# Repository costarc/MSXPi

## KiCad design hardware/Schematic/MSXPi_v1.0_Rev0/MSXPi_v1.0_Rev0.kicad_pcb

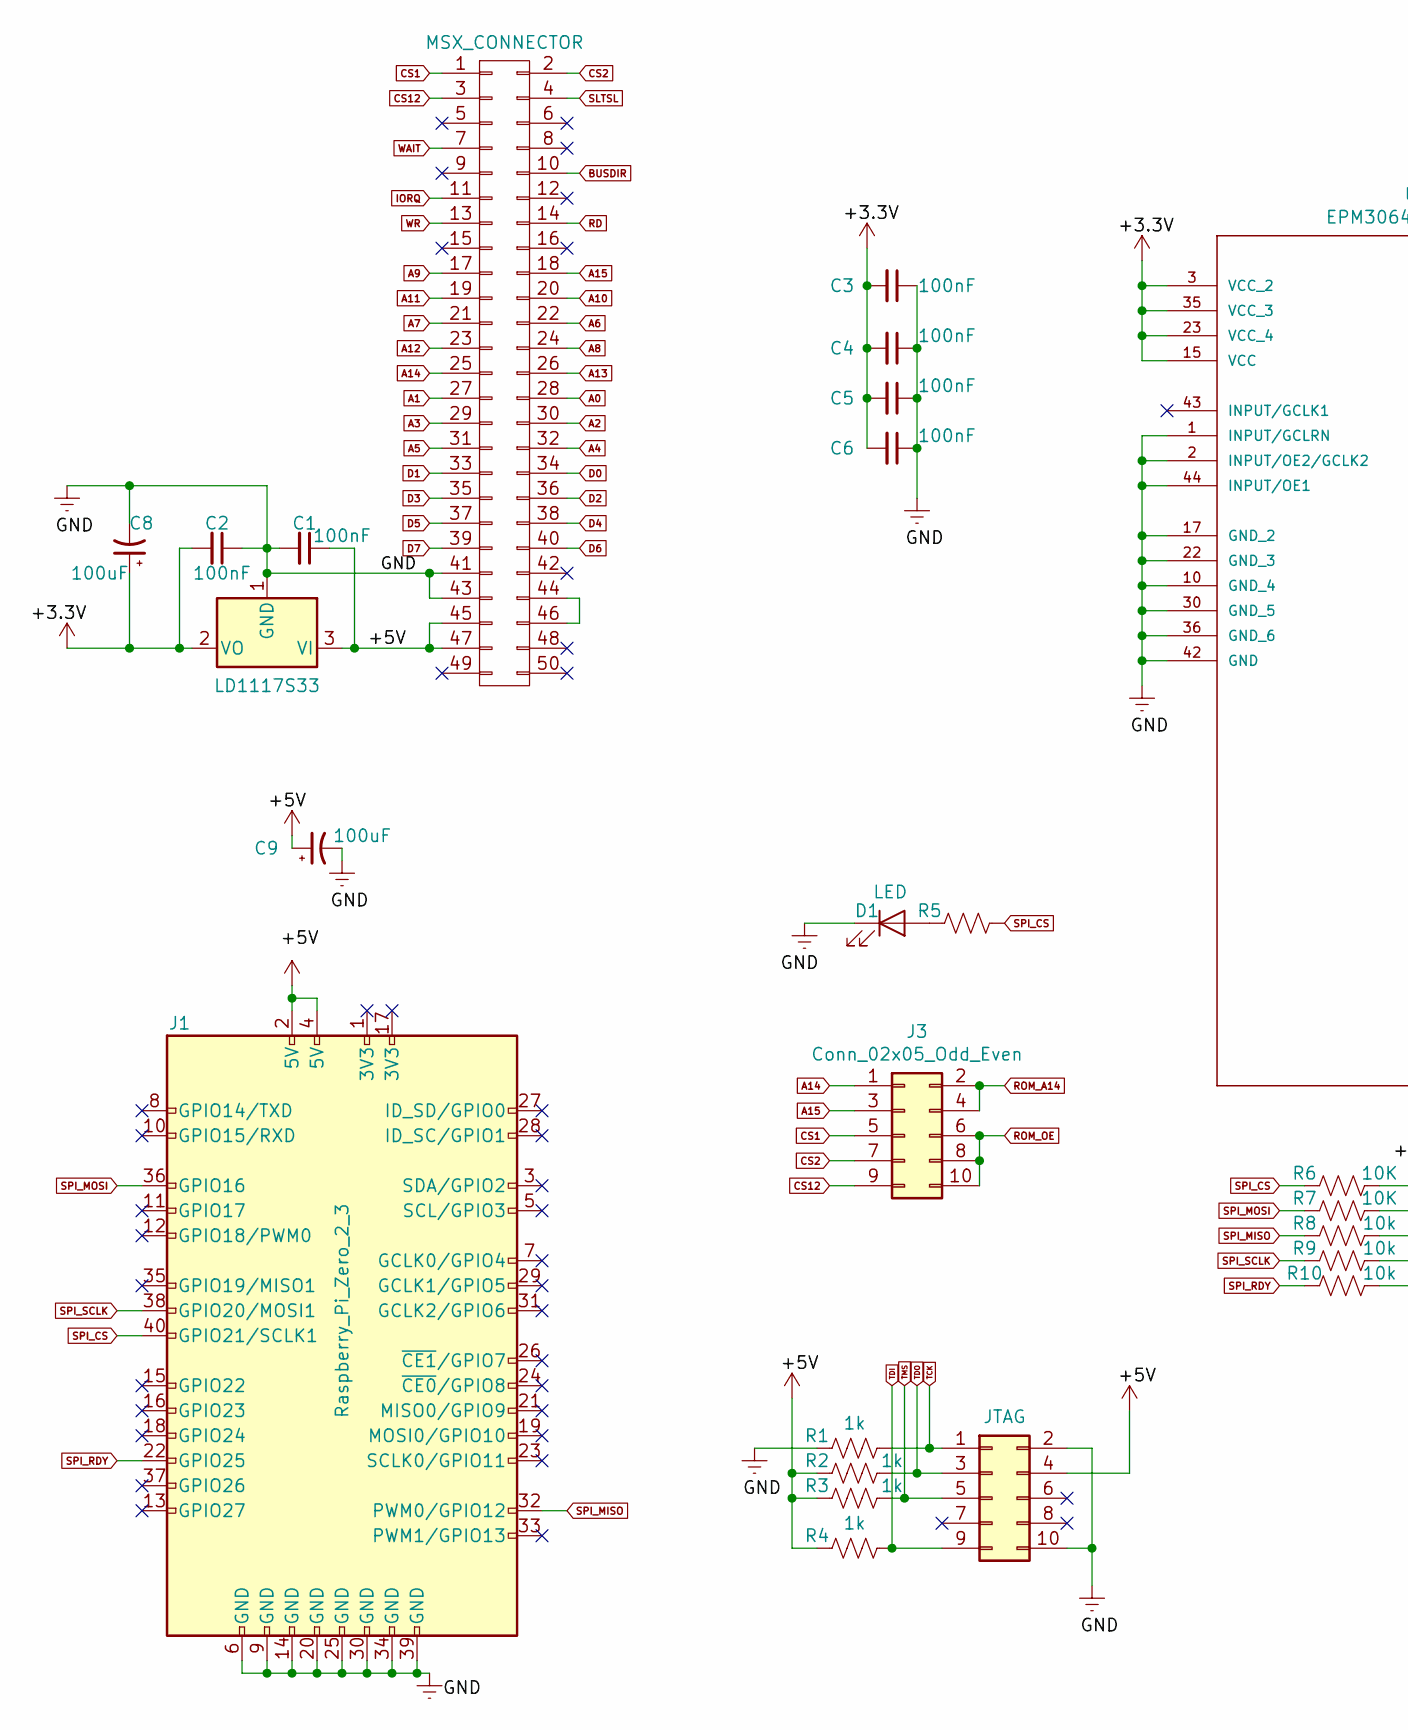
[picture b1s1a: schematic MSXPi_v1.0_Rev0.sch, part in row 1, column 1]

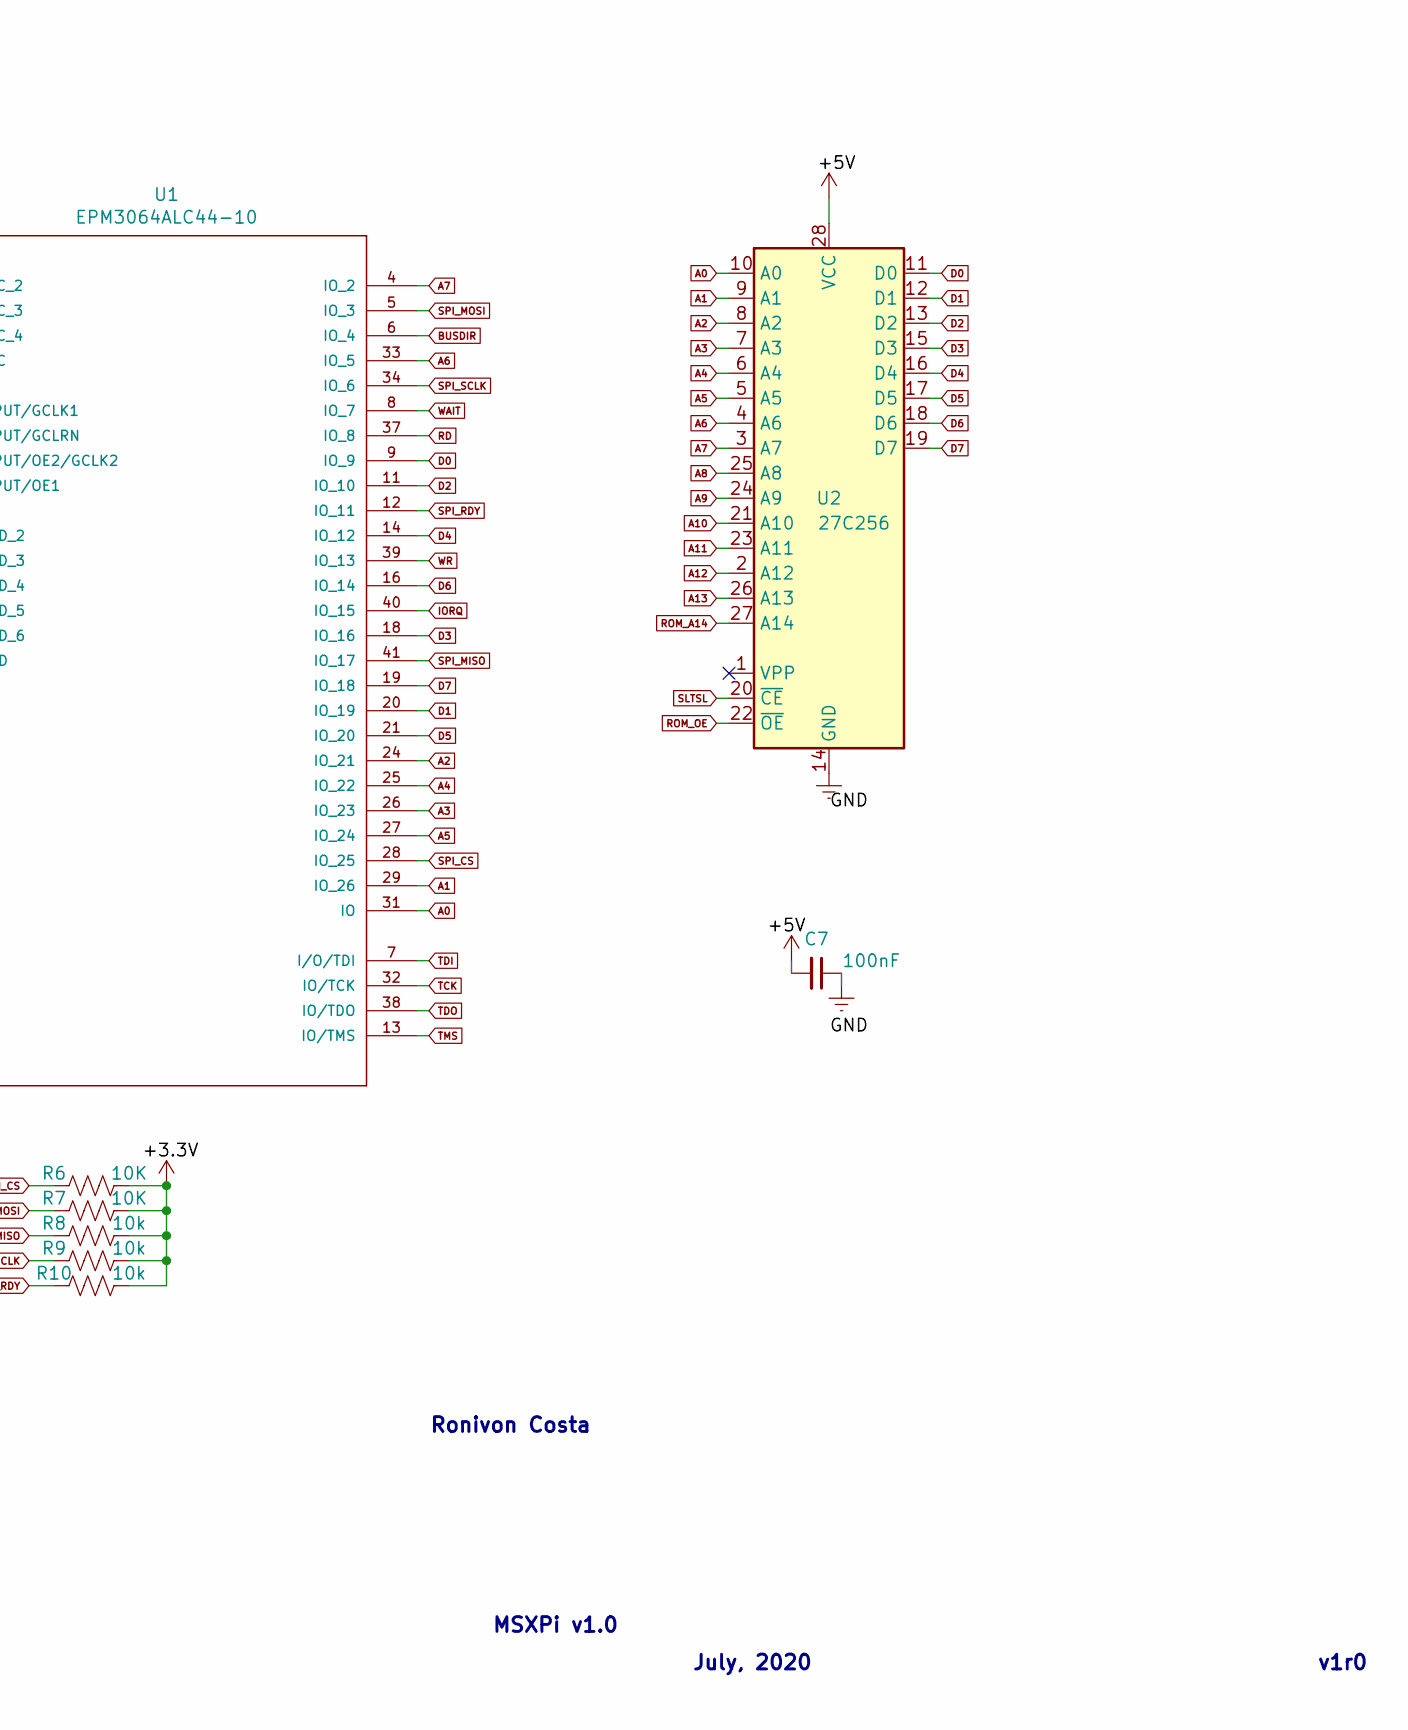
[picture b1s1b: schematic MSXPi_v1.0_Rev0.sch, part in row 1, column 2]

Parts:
C1, C2, C3, C4, C5, C6, C7: 100nF; C_Disc_D3.0mm_W1.6mm_P2.50mm
C8, C9: 100uF; CP_Radial_D5.0mm_P2.50mm
D1: LED; LED_D3.0mm
J1: Raspberry_Pi_Zero_2_3; PinHeader_2x20_P2.54mm_Vertical
J2: JTAG; IDC-Header_2x05_P2.54mm_Horizontal
J3: Conn_02x05_Odd_Even; JST_PHD_B10B-PHDSS_2x05_P2.00mm_Vertical
LD1117S33: LD1117S33TR_SOT223; SOT-223-3_TabPin2
P1: MSX_CONNECTOR; card_edge_connector
R1, R2, R3, R4: 1k; R_Axial_DIN0204_L3.6mm_D1.6mm_P5.08mm_Horizontal
R5: R_US; R_Axial_DIN0204_L3.6mm_D1.6mm_P5.08mm_Horizontal
R6, R7: 10K; R_Axial_DIN0204_L3.6mm_D1.6mm_P5.08mm_Horizontal
R8, R9, R10: 10k; R_Axial_DIN0204_L3.6mm_D1.6mm_P5.08mm_Horizontal
U1: EPM3064ALC44-10; PLCC-44_THT-Socket
U2: 27C256; DIP-28_W15.24mm

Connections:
+3V3: C2.2, C3.2, C4.2, C5.2, C6.2, C8.1, LD1117S33.2 (VO), R6.2, R7.2, R8.2, R9.2, R10.2, U1.3 (VCC_2), U1.15 (VCC), U1.23 (VCC_4), U1.35 (VCC_3)
+5V: C1.1, C7.2, C9.1, J1.2 (5V), J1.4 (5V), J2.4, LD1117S33.3 (VI), P1.45, P1.47, R2.2, R3.2, R4.2, U2.28 (VCC)
A0: P1.28, U1.31 (IO), U2.10 (A0)
A1: P1.27, U1.29 (IO_26), U2.9 (A1)
A2: P1.30, U1.24 (IO_21), U2.8 (A2)
A3: P1.29, U1.26 (IO_23), U2.7 (A3)
A4: P1.32, U1.25 (IO_22), U2.6 (A4)
A5: P1.31, U1.27 (IO_24), U2.5 (A5)
A6: P1.22, U1.33 (IO_5), U2.4 (A6)
A7: P1.21, U1.4 (IO_2), U2.3 (A7)
A8: P1.24, U2.25 (A8)
A9: P1.17, U2.24 (A9)
A10: P1.20, U2.21 (A10)
A11: P1.19, U2.23 (A11)
A12: P1.23, U2.2 (A12)
A13: P1.26, U2.26 (A13)
A14: J3.1, P1.25
A15: J3.3, P1.18
BUSDIR: P1.10, U1.6 (IO_4)
CS1: J3.5, P1.1
CS2: J3.7, P1.2
CS12: J3.9, P1.3
D0: P1.34, U1.9 (IO_9), U2.11 (D0)
D1: P1.33, U1.20 (IO_19), U2.12 (D1)
D2: P1.36, U1.11 (IO_10), U2.13 (D2)
D3: P1.35, U1.18 (IO_16), U2.15 (D3)
D4: P1.38, U1.14 (IO_12), U2.16 (D4)
D5: P1.37, U1.21 (IO_20), U2.17 (D5)
D6: P1.40, U1.16 (IO_14), U2.18 (D6)
D7: P1.39, U1.19 (IO_18), U2.19 (D7)
GNDREF: C1.2, C2.1, C3.1, C4.1, C5.1, C6.1, C7.1, C8.2, C9.2, D1.1 (K), J1.6 (GND), J1.9 (GND), J1.14 (GND), J1.20 (GND), J1.25 (GND), J1.30 (GND), J1.34 (GND), J1.39 (GND), J2.2, J2.10, LD1117S33.1 (GND), P1.41, P1.43, R1.1, U1.1 (INPUT/GCLRN), U1.2 (INPUT/OE2/GCLK2), U1.10 (GND_4), U1.17 (GND_2), U1.22 (GND_3), U1.30 (GND_5), U1.36 (GND_6), U1.42 (GND), U1.44 (INPUT/OE1), U2.14 (GND)
IORQ: P1.11, U1.40 (IO_15)
unnamed: D1.2 (A), R5.1
unnamed: P1.44, P1.46
RD: P1.14, U1.37 (IO_8)
ROM_A14: J3.2, J3.4, U2.27 (A14)
ROM_OE: J3.6, J3.8, J3.10, U2.22 (~OE)
SLTSL: P1.4, U2.20 (~CE)
SPI_CS: J1.40 (GPIO21/SCLK1), R5.2, R6.1, U1.28 (IO_25)
SPI_MISO: J1.32 (PWM0/GPIO12), R8.1, U1.41 (IO_17)
SPI_MOSI: J1.36 (GPIO16), R7.1, U1.5 (IO_3)
SPI_RDY: J1.22 (GPIO25), R10.1, U1.12 (IO_11)
SPI_SCLK: J1.38 (GPIO20/MOSI1), R9.1, U1.34 (IO_6)
TCK: J2.1, R1.2, U1.32 (IO/TCK)
TDI: J2.9, R4.1, U1.7 (I/O/TDI)
TDO: J2.3, R2.1, U1.38 (IO/TDO)
TMS: J2.5, R3.1, U1.13 (IO/TMS)
WAIT: P1.7, U1.8 (IO_7)
WR: P1.13, U1.39 (IO_13)

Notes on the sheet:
MSXPi v1.0
July, 2020
v1r0
Ronivon Costa

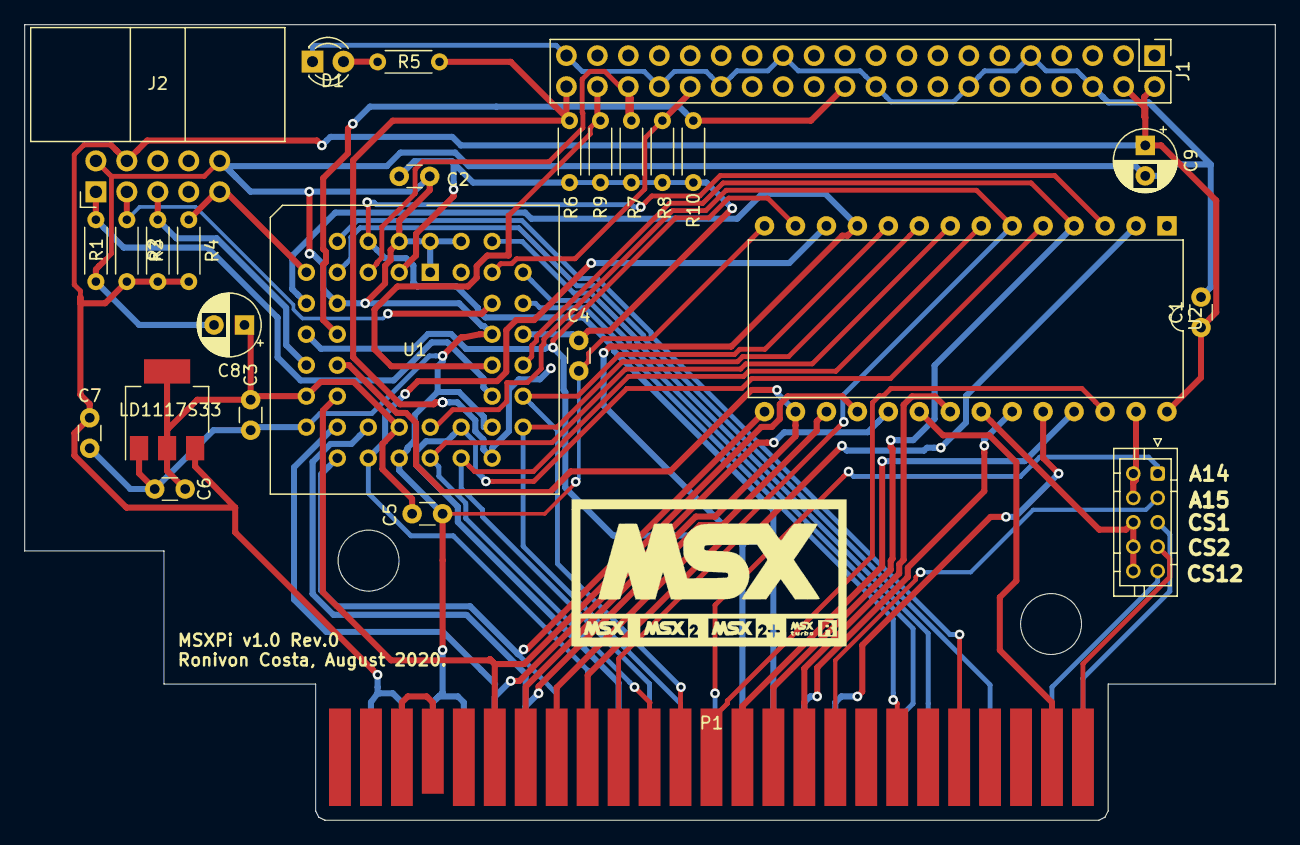
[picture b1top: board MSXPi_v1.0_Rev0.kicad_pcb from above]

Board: 2 copper layers, 102.6 x 65.3 mm, 27 parts (0 on the bottom side), 49 nets.

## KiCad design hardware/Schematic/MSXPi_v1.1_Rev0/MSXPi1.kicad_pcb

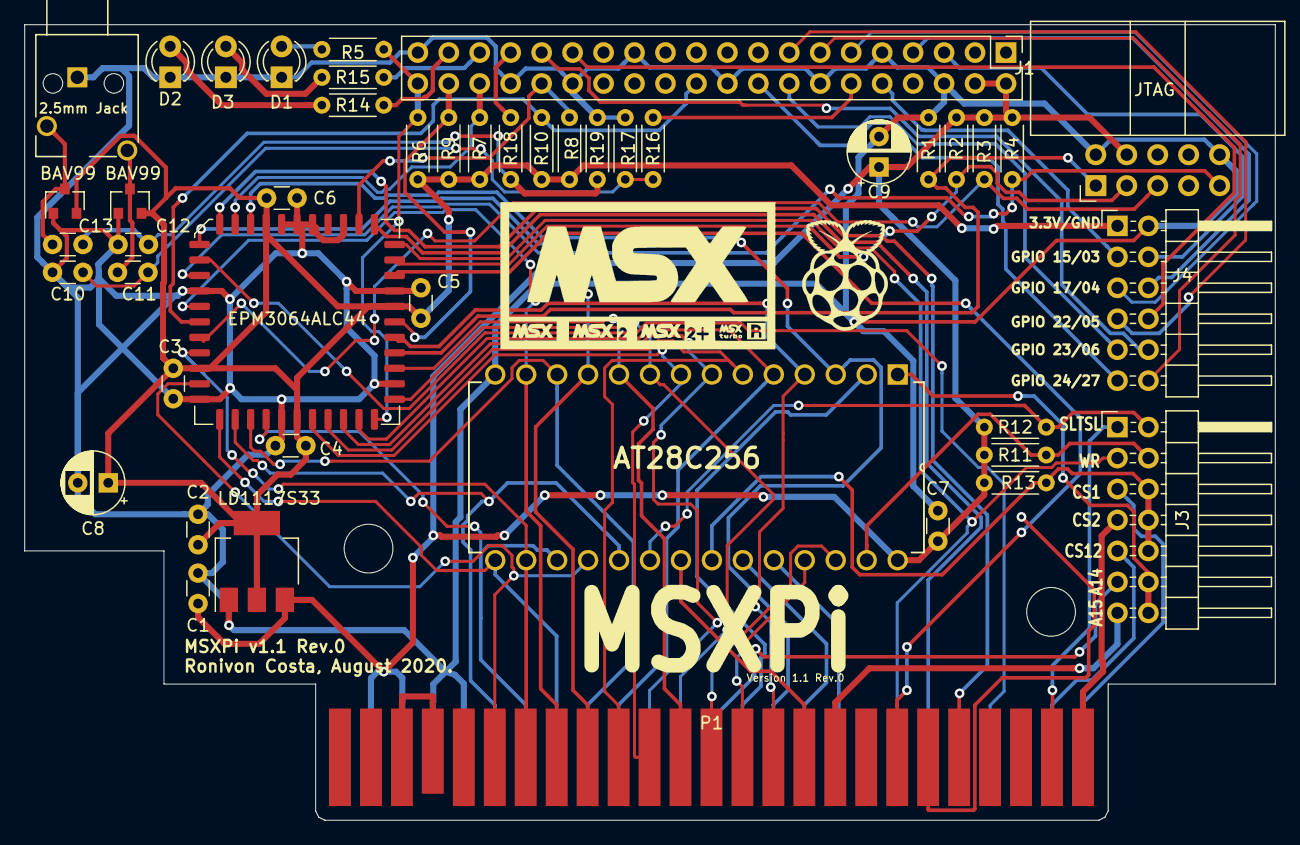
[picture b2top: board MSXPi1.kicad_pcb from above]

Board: 2 copper layers, 102.6 x 65.3 mm, 46 parts (0 on the bottom side), 71 nets.

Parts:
2.5mm Jack: SJ-2509N; CUI_SJ-2509N
AT28C256: AT28C256-15PU; DIP254P1524X482-28
BAV99, BAV99#2: BAV99; SOT-23
C1, C2, C3, C4, C5, C6, C7: 100nF; C_Disc_D3.0mm_W1.6mm_P2.50mm
C8, C9: 100uF; CP_Radial_D5.0mm_P2.50mm
C10, C12: 33nF; C_Disc_D3.0mm_W1.6mm_P2.50mm
C11, C13: 10uF; C_Disc_D3.0mm_W1.6mm_P2.50mm
D1, D2, D3: LED; LED_D3.0mm
EPM3064ALC44: EPM3064ALC44-10; PLCC-44_16.6x16.6mm_P1.27mm
J1: Raspberry_Pi_Zero_2_3; PinHeader_2x20_P2.54mm_Vertical
J3: Conn_02x07_Odd_Even; PinHeader_2x07_P2.54mm_Horizontal
J4: Conn_02x06_Odd_Even; PinHeader_2x06_P2.54mm_Horizontal
JTAG: JTAG; IDC-Header_2x05_P2.54mm_Horizontal
LD1117S33: LD1117S33TR_SOT223; SOT-223-3_TabPin2
P1: MSX_CONNECTOR; card_edge_connector
R1, R2, R3, R4: 1k; R_Axial_DIN0204_L3.6mm_D1.6mm_P5.08mm_Horizontal
R5, R14, R15, R16, R18: 270R; R_Axial_DIN0204_L3.6mm_D1.6mm_P5.08mm_Horizontal
R6, R7: 10K; R_Axial_DIN0204_L3.6mm_D1.6mm_P5.08mm_Horizontal
R8, R9, R10, R11, R12, R13: 10k; R_Axial_DIN0204_L3.6mm_D1.6mm_P5.08mm_Horizontal
R17, R19: 150R; R_Axial_DIN0204_L3.6mm_D1.6mm_P5.08mm_Horizontal

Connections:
+3V3: BAV99.2, BAV99#2.2, C2.2, C3.2, C4.2, C5.2, C6.2, C8.1, EPM3064ALC44.3, EPM3064ALC44.15, EPM3064ALC44.23, EPM3064ALC44.35, J4.1, LD1117S33.2, R6.2, R7.2, R8.2, R9.2, R10.2
+5V: AT28C256.28, C1.1, C7.2, C9.1, J1.2, J1.4, JTAG.4, LD1117S33.3, P1.45, P1.47, R2.2, R3.2, R4.2, R11.2, R12.2, R13.2
A0: AT28C256.10, EPM3064ALC44.31, P1.28
A1: AT28C256.9, EPM3064ALC44.29, P1.27
A2: AT28C256.8, EPM3064ALC44.24, P1.30
A3: AT28C256.7, EPM3064ALC44.26, P1.29
A4: AT28C256.6, EPM3064ALC44.25, P1.32
A5: AT28C256.5, EPM3064ALC44.27, P1.31
A6: AT28C256.4, EPM3064ALC44.33, P1.22
A7: AT28C256.3, EPM3064ALC44.4, P1.21
A8: AT28C256.25, P1.24
A9: AT28C256.24, P1.17
A10: AT28C256.21, P1.20
A11: AT28C256.23, P1.19
A12: AT28C256.2, P1.23
A13: AT28C256.26, P1.26
A14: J3.11, P1.25
A15: J3.13, P1.18
BUSDIR: EPM3064ALC44.6, P1.10
CS1: J3.5, P1.1
CS2: J3.7, P1.2
CS12: J3.9, P1.3
D0: AT28C256.11, EPM3064ALC44.9, P1.34
D1: AT28C256.12, EPM3064ALC44.20, P1.33
D2: AT28C256.13, EPM3064ALC44.11, P1.36
D3: AT28C256.15, EPM3064ALC44.18, P1.35
D4: AT28C256.16, EPM3064ALC44.14, P1.38
D5: AT28C256.17, EPM3064ALC44.21, P1.37
D6: AT28C256.18, EPM3064ALC44.16, P1.40
D7: AT28C256.19, EPM3064ALC44.19, P1.39
GNDREF: 2.5mm Jack.1, AT28C256.14, BAV99.1, BAV99#2.1, C1.2, C2.1, C3.1, C4.1, C5.1, C6.1, C7.1, C8.2, C9.2, C10.1, C12.1, D1.1, D2.1, D3.1, EPM3064ALC44.1, EPM3064ALC44.2, EPM3064ALC44.10, EPM3064ALC44.17, EPM3064ALC44.22, EPM3064ALC44.30, EPM3064ALC44.36, EPM3064ALC44.42, EPM3064ALC44.44, J1.6, J1.9, J1.14, J1.20, J1.25, J1.30, J1.34, J1.39, J4.2, JTAG.2, JTAG.10, LD1117S33.1, P1.41, P1.43, R1.1, R17.2, R19.2
GPIO3: J1.5, J4.4
GPIO4: J1.7, J4.6
GPIO5: J1.29, J4.8
GPIO6: J1.31, J4.10
GPIO15: J1.10, J4.3
GPIO17: J1.11, J4.5
GPIO22: J1.15, J4.7
GPIO23: J1.16, J4.9
GPIO24: J1.18, J4.11
GPIO27: J1.13, J4.12
IORQ: EPM3064ALC44.40, P1.11
unnamed: C10.2, C11.2, R16.2, R17.1
unnamed: 2.5mm Jack.3, BAV99#2.3, C11.1
unnamed: C12.2, C13.2, R18.2, R19.1
unnamed: 2.5mm Jack.2, BAV99.3, C13.1
unnamed: D1.2, R5.1
unnamed: D2.2, R14.1
unnamed: D3.2, R15.1
unnamed: P1.44, P1.46
PWM0: J1.12, R16.1
PWM1: J1.33, R18.1
RD: EPM3064ALC44.37, P1.14
ROM_A14: AT28C256.1, J3.12, J3.14
RPI_BUSY: J1.35, R15.2
RPI_ON: J1.37, R14.2
SLTSL: J3.1, P1.4
SPI_CS: EPM3064ALC44.28, J1.40, R5.2, R6.1
SPI_MISO: EPM3064ALC44.41, J1.32, R8.1
SPI_MOSI: EPM3064ALC44.5, J1.36, R7.1
SPI_RDY: EPM3064ALC44.12, J1.22, R10.1
SPI_SCLK: EPM3064ALC44.34, J1.38, R9.1
TCK: EPM3064ALC44.32, JTAG.1, R1.2
TDI: EPM3064ALC44.7, JTAG.9, R4.1
TDO: EPM3064ALC44.38, JTAG.3, R2.1
TMS: EPM3064ALC44.13, JTAG.5, R3.1
WAIT: EPM3064ALC44.8, P1.7
WR: EPM3064ALC44.39, J3.3, P1.13
mem_ce: AT28C256.20, J3.2, R12.1
mem_oe: AT28C256.22, J3.6, J3.8, J3.10, R13.1
mem_we: AT28C256.27, J3.4, R11.1
